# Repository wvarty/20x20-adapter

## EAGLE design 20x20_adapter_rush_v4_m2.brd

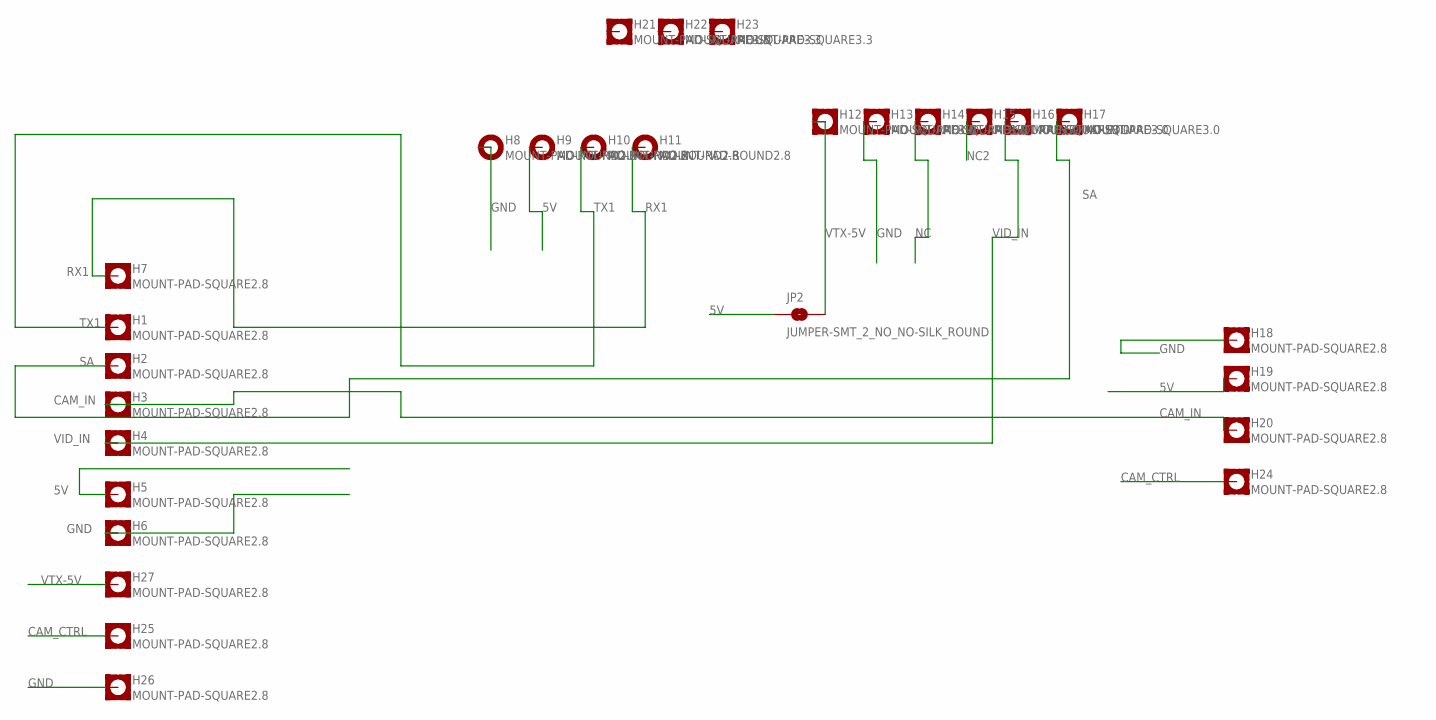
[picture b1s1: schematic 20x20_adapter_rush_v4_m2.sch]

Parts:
H1, H2, H3, H4, H5, H6, H7, H18, H19, H20, H24, H25, H26, H27: MOUNT-PAD-SQUARE2.8; 2,8-PAD-SQUARE
H8, H9, H10, H11: MOUNT-PAD-ROUND2.8; 1,0-PAD
H12, H13, H14, H15, H16, H17: MOUNT-PAD-SQUARE3.0; 1,5-PAD-SQUARE
H21, H22, H23: MOUNT-PAD-SQUARE3.3; 3,3-PAD-SQUARE
JP2: JUMPER-SMT_2_NO_NO-SILK_ROUND; SMT-JUMPER_2_NO_NO-SILK_ROUND

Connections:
5V: H5.P$2, H9.B1,0, H19.P$2, JP2.1
CAM_CTRL: H24.P$2, H25.P$2
CAM_IN: H3.P$2, H20.P$2
GND: H6.P$2, H8.B1,0, H13.P$1, H18.P$2, H26.P$2
NC: H14.P$1
NC2: H15.P$1
RX1: H7.P$2, H11.B1,0
SA: H2.P$2, H17.P$1
TX1: H1.P$2, H10.B1,0
VID_IN: H4.P$2, H16.P$1
VTX-5V: H12.P$1, H27.P$2, JP2.2

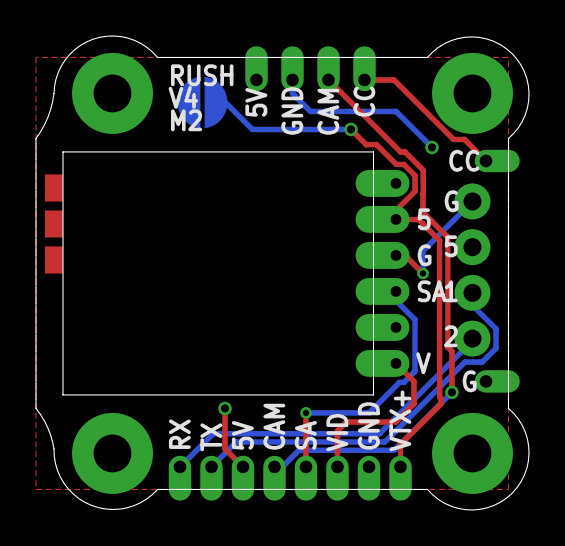
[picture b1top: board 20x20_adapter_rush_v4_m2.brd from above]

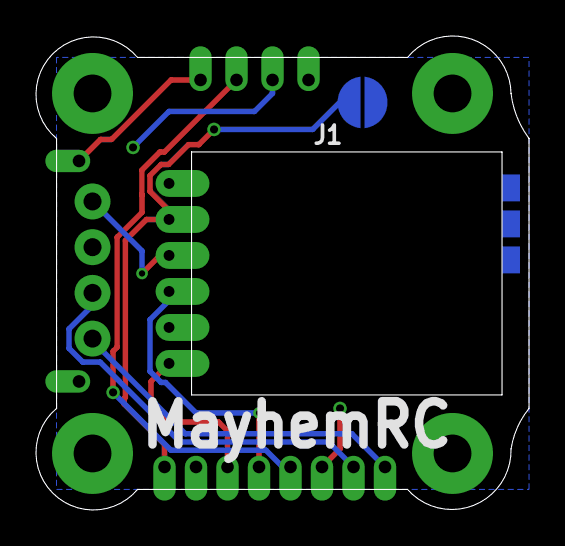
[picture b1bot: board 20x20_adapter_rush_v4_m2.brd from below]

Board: 2 copper layers, 27.4 x 26.3 mm, 28 parts (2 on the bottom side), 9 nets.

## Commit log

2020-11-14 Added v4 PCB with MayhemRC branding
2020-11-14 Added v4 gerbers

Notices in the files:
parts and their libraries:
SparkFun-Jumpers: Licensing: Creative Commons ShareAlike 4.0 International - https://creativecommons.org/licenses/by-sa/4.0
